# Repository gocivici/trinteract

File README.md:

# Trinteract

This repository contains all the files and documentation for Trinteract, An open-source Arduino-compatible 3DOF Human Interface Device (HID). In other words a joystick that's capable of moving in all 3 Dimensions. Trinteract uses a 3D magnetometer and a Neodymium magnet to detect motion in 3D space.  [Visit the DIY guide](https://www.instructables.com/Trinteract-an-Open-source-3D-Input-Device/)

[Watch the Demo here](https://youtu.be/YoGgdORVARs)

File structure:
+  `Software` contains the arduino code and necessary drivers 
+  `PCB` contains the KiCAD PCB files and gerber files for manufacturing
+  `docs` contains the source code for the documentation website build with [Sphinx](https://www.sphinx-doc.org/en/master/index.html)
+  `CAD` contains all fusion360 CAD files and print ready .stl files  

Before Assembly            |  Assembled
:-------------------------:|:-------------------------:
  |  

<p align="center" width="100%">
<a href="https://certification.oshwa.org/ee000001.html">[OSHW] EE00001 | Certified open source hardware</a>
</p>

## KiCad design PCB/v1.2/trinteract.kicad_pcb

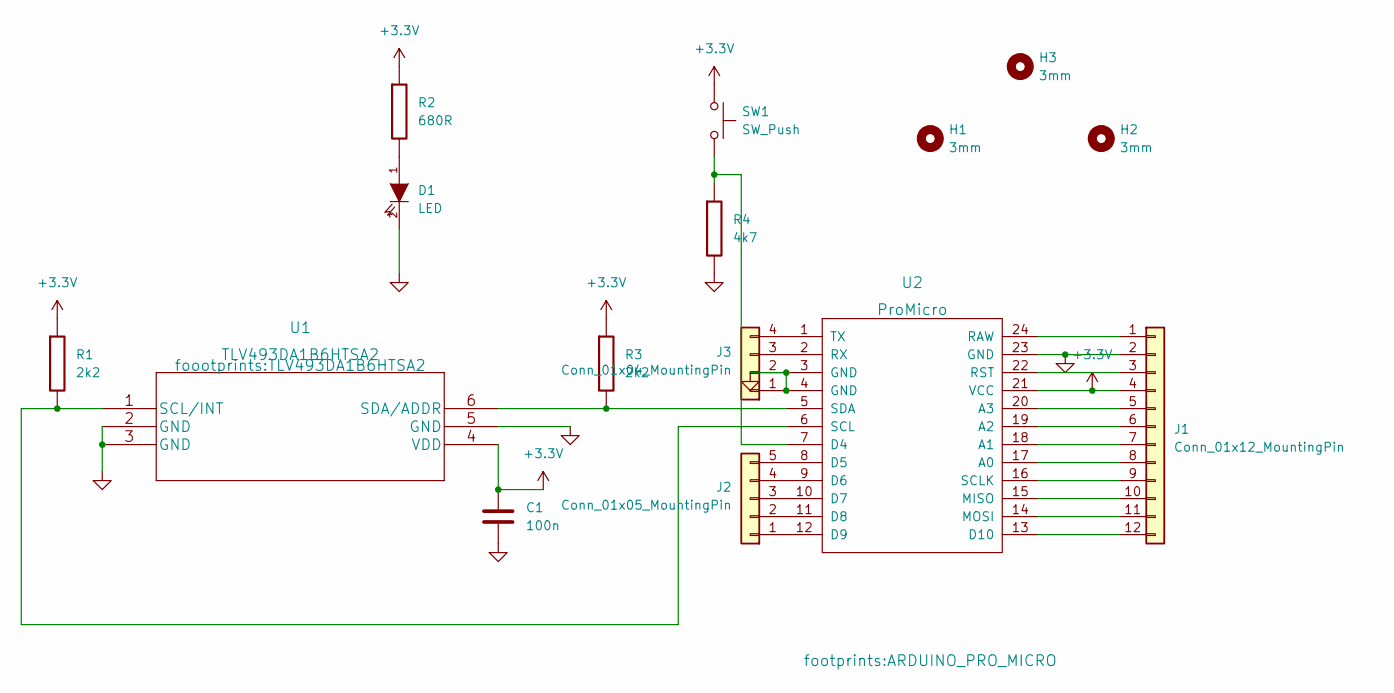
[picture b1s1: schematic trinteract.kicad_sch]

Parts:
C1: 100n; C_0805_2012Metric_Pad1.18x1.45mm_HandSolder
D1: LED; 156120GS82500
H1, H2, H3: 3mm; MountingHole_3.2mm_M3_DIN965_Pad
J1: Conn_01x12_MountingPin; PinHeader_1x12_P2.54mm_Horizontal
J2: Conn_01x05_MountingPin; PinHeader_1x05_P2.54mm_Horizontal
J3: Conn_01x04_MountingPin; PinHeader_1x04_P2.54mm_Horizontal
R1, R3: 2k2; R_0805_2012Metric_Pad1.20x1.40mm_HandSolder
R2: 680R; R_0805_2012Metric_Pad1.20x1.40mm_HandSolder
R4: 4k7; R_0805_2012Metric_Pad1.20x1.40mm_HandSolder
SW1: SW_Push; SW_SPST_TL3342
U1: TLV493DA1B6HTSA2
U2: ProMicro; ARDUINO_PRO_MICRO

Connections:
+3.3V: C1.1, J1.4, R1.1, R2.1, R3.1, SW1.1, U1.4 (VDD), U2.21 (VCC)
GND: C1.2, D1.2 (K), J1.2, J3.1, J3.2, R4.2, U1.2 (GND), U1.3 (GND), U1.5 (GND), U2.3 (GND), U2.4 (GND), U2.23 (GND)
unnamed: D1.1 (A), R2.2
unnamed: R1.2, U1.1 (SCL/INT), U2.6 (SCL)
unnamed: R3.2, U1.6 (SDA/ADDR), U2.5 (SDA)
unnamed: R4.1, SW1.2, U2.7 (D4)
unnamed: J3.4, U2.1 (TX)
unnamed: J3.3, U2.2 (RX)
unnamed: J2.5, U2.8 (D5)
unnamed: J2.4, U2.9 (D6)
unnamed: J2.3, U2.10 (D7)
unnamed: J2.2, U2.11 (D8)
unnamed: J2.1, U2.12 (D9)
unnamed: J1.12, U2.13 (D10)
unnamed: J1.11, U2.14 (MOSI)
unnamed: J1.10, U2.15 (MISO)
unnamed: J1.9, U2.16 (SCLK)
unnamed: J1.8, U2.17 (A0)
unnamed: J1.7, U2.18 (A1)
unnamed: J1.6, U2.19 (A2)
unnamed: J1.5, U2.20 (A3)
unnamed: J1.3, U2.22 (RST)
unnamed: J1.1, U2.24 (RAW)

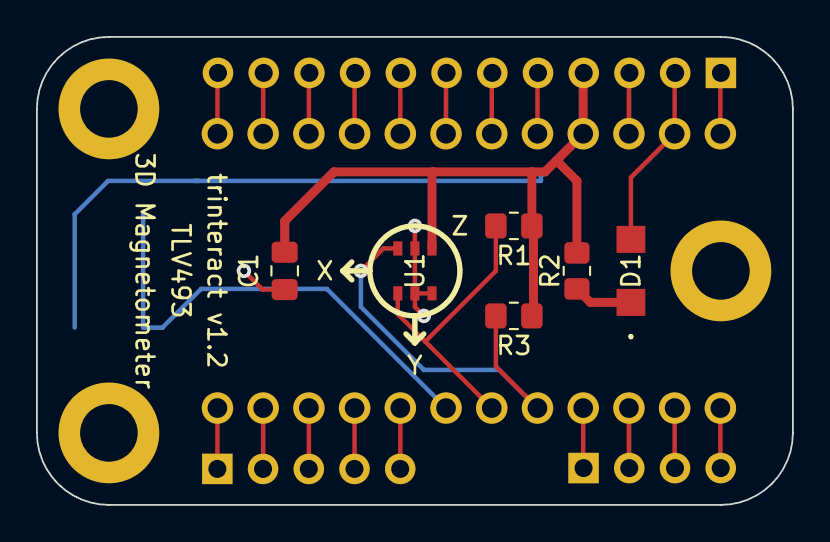
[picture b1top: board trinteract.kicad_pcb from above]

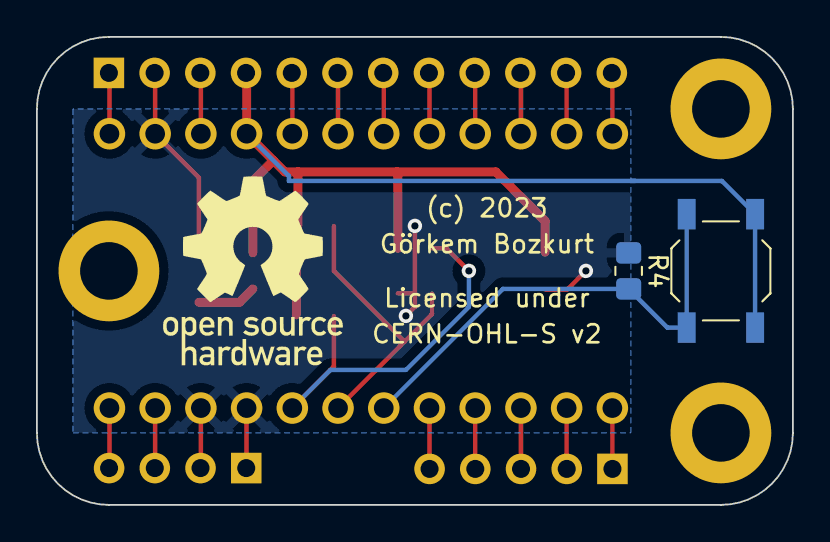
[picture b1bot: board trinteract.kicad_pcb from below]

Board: 2 copper layers, 42.0 x 26.0 mm, 15 parts (5 on the bottom side), 23 nets.

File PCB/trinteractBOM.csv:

Id,Designator,Package,Quantity,Designation,Supplier and ref
1,D1,156120GS82500,1,LED,
2,"R3,R1",R_0805_2012Metric_Pad1.20x1.40mm_HandSolder,2,2k2,
3,R2,R_0805_2012Metric_Pad1.20x1.40mm_HandSolder,1,680R,
4,U1,TLV493DA1B6HTSA2,1,TLV493DA1B6HTSA2,
5,C1,C_0805_2012Metric_Pad1.18x1.45mm_HandSolder,1,100n,
6,U2,ARDUINO_PRO_MICRO,1,ProMicro,
7,SW1,SW_SPST_TL3342,1,SW_Push,
8,J3,Female_Header_1x12-Pin_P2.54mm_Horizontal,2,1x12,
9,R4,R_0805_2012Metric_Pad1.20x1.40mm_HandSolder,1,4k7,

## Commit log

2023-04-29 updated index file
2023-04-29 changed directory
2023-04-29 added nojekyll file
2023-04-29 font change
2023-04-30 update index
2023-05-08 added gerber files for manufacturing
2023-05-08 updated arduino code
2023-05-08 Create LICENSE
2023-05-08 update OHL
2023-05-08 updating docs
2023-05-08 added license
2023-05-08 update license
2023-05-09 removed fullscreen mode
2023-05-09 remove fullscreen button
2023-05-09 added media
2023-05-09 added file structure
2023-05-09 added stl files
2023-05-10 added new doc pages
2023-05-10 project name update
2023-05-11 updated docs
2023-05-11 update wiki
2023-05-17 added BOM
2023-05-17 added gif
2023-05-17 updated file
2023-05-17 updated gif
2023-05-17 updated wiki
2023-05-19 added demo video
2023-05-30 update docs
2023-05-30 added video
2023-06-26 edited wiki and added 3D files
2023-06-26 edited link
2023-06-26 edited some info

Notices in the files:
PCB/v1.2/trinteract.kicad_pcb:
(c) 2023
CERN-OHL-S v2
Licensed under
B.SilkS
README.md:
License: CERN-OHL-S
License: MIT
License: CC BY-SA 4.0
parts and their libraries:
Copyright 2021 Accelerated Designs. All rights reserved.
